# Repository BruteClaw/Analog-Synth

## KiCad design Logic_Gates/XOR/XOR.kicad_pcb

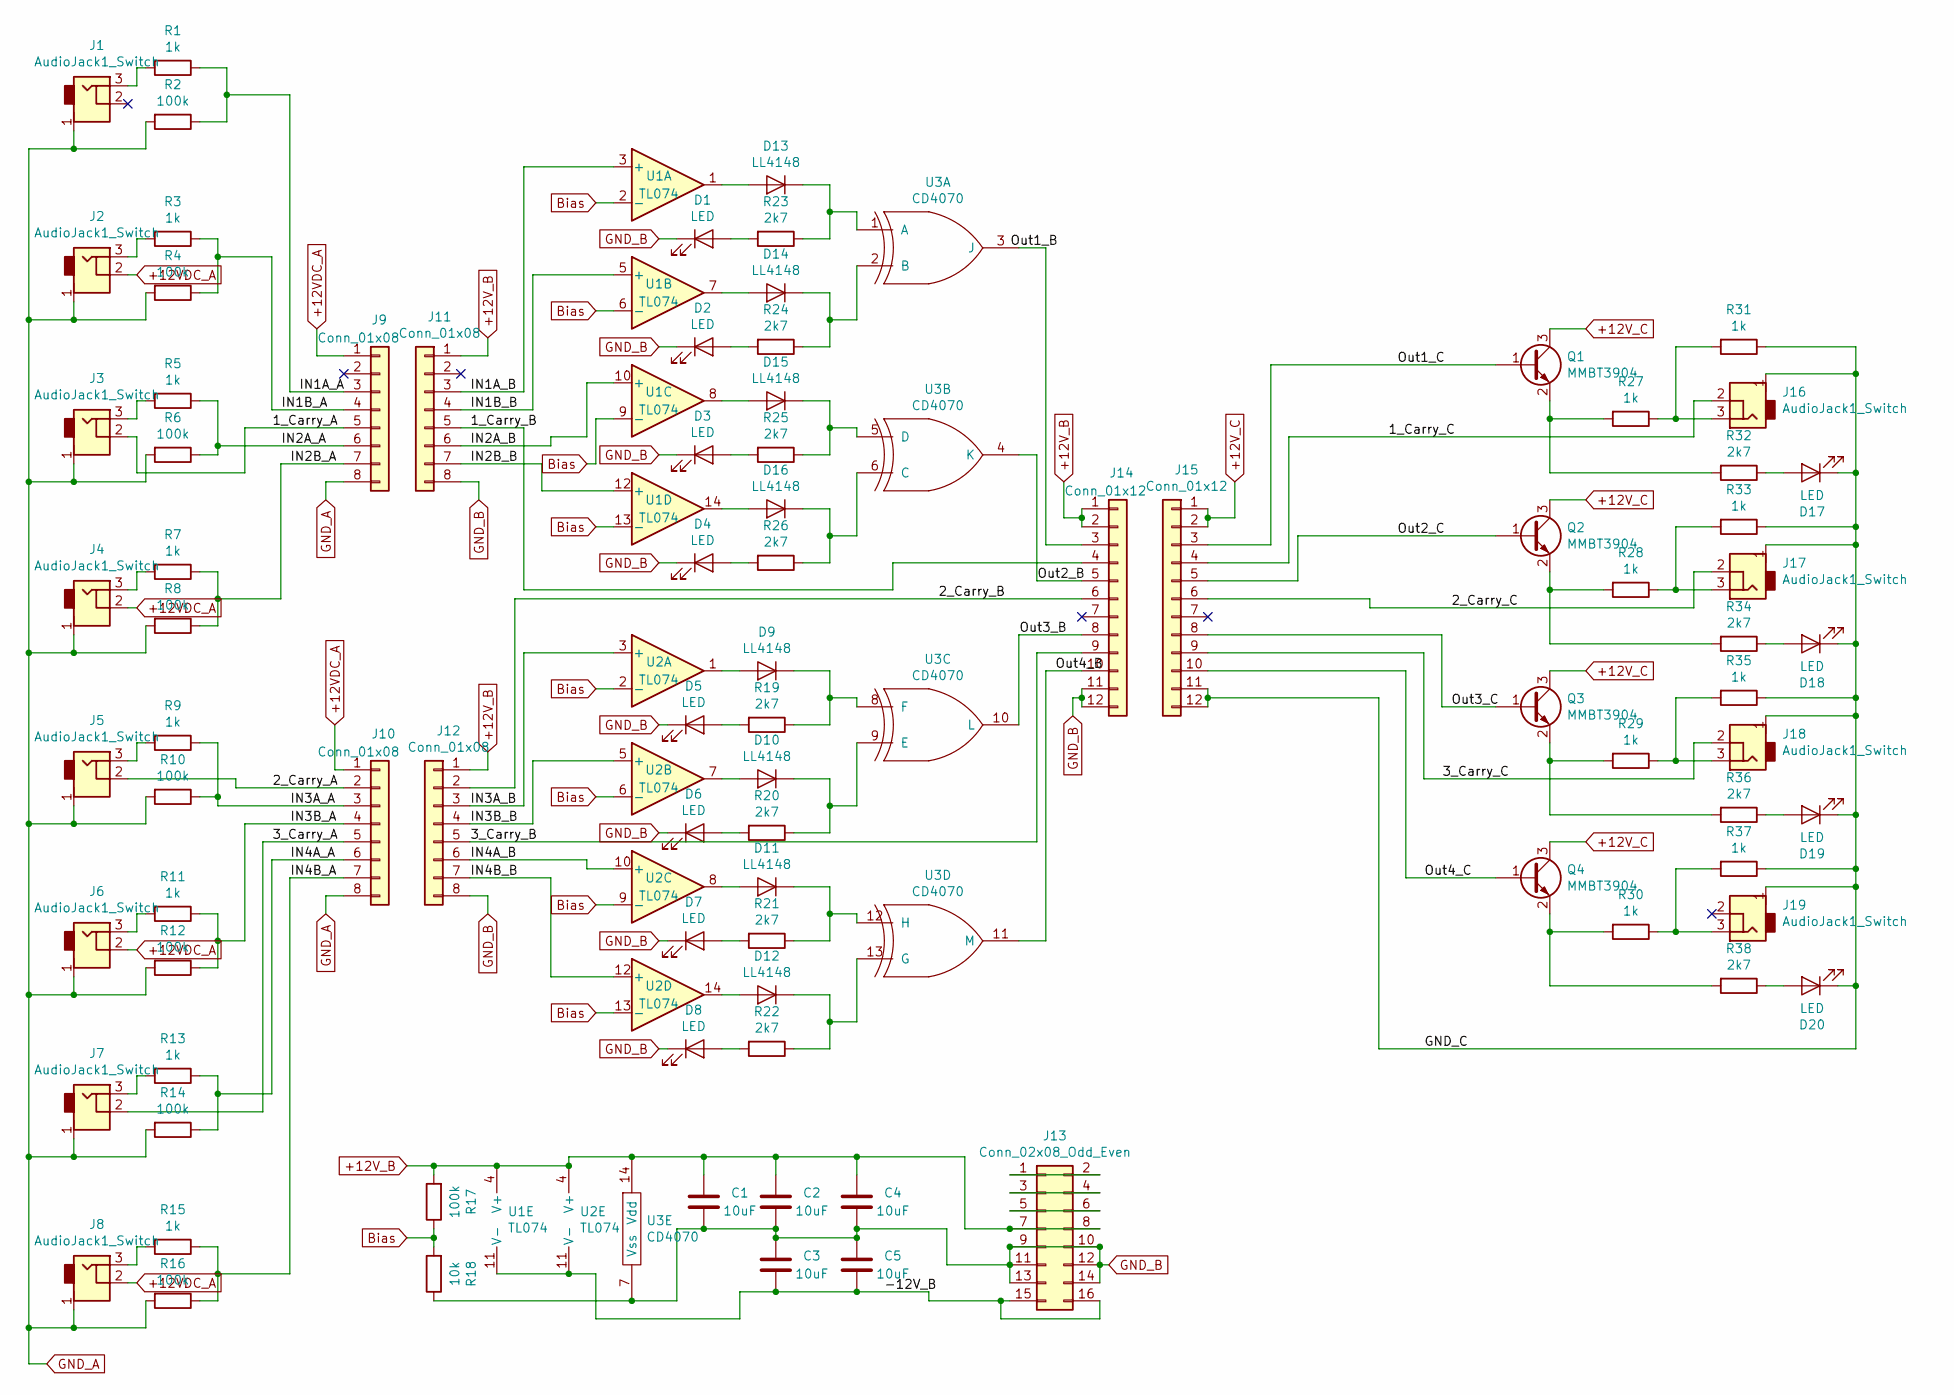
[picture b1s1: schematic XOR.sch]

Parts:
C1, C2, C3, C4, C5: 10uF; C_1210_HandSoldering
D1, D2, D3, D4, D5, D6, D7, D8, D17, D18, D19, D20: LED; LED_Rectangular_W3.9mm_H1.9mm
D9, D10, D11, D12, D13, D14, D15, D16: LL4148; D_MiniMELF_Handsoldering
J1, J2, J3, J4, J5, J6, J7, J8, J16, J17, J18, J19: AudioJack1_Switch; Mono_Jack_3.5mm_Switch_Switchcraft_35RAPC2AH3
J9, J10, J11, J12: Conn_01x08; Pin_Header_Straight_1x08_Pitch2.54mm
J13: Conn_02x08_Odd_Even; Pin_Header_Straight_2x08_Pitch2.54mm
J14, J15: Conn_01x12; Pin_Header_Straight_1x12_Pitch2.54mm
Q1, Q2, Q3, Q4: MMBT3904; SOT-23
R1, R3, R5, R7, R9, R11, R13, R15, R27, R28, R29, R30, R31, R33, R35, R37: 1k; R_1210_HandSoldering
R2, R4, R6, R8, R10, R12, R14, R16, R17: 100k; R_1210_HandSoldering
R18: 10k; R_1210_HandSoldering
R19, R20, R21, R22, R23, R24, R25, R26, R32, R34, R36, R38: 2k7; R_1210_HandSoldering
U1, U2: TL074; SOIC-14_3.9x8.7mm_Pitch1.27mm
U3: CD4070; SOIC-14_3.9x8.7mm_Pitch1.27mm

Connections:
+12VDC_A: J2.2, J4.2, J6.2, J8.2, J9.1, J10.1
+12V_B: C1.2, C2.2, C4.2, J11.1, J12.1, J13.7, J13.8, J14.1, J14.2, R17.2, U1.4 (V+), U2.4 (V+), U3.14 (Vdd)
+12V_C: J15.1, J15.2, Q1.3 (C), Q2.3 (C), Q3.3 (C), Q4.3 (C)
/1_Carry_A: J3.2, J9.5
/1_Carry_B: J11.5, J14.4
/1_Carry_C: J15.4, J16.2
/2_Carry_A: J5.2, J10.2
/2_Carry_B: J12.2, J14.6
/2_Carry_C: J15.6, J17.2
/3_Carry_A: J7.2, J10.5
/3_Carry_B: J12.5, J14.9
/3_Carry_C: J15.9, J18.2
/-12V_B: C3.1, C5.1, J13.15, J13.16, U1.11 (V-), U2.11 (V-)
/GND_C: D17.1 (K), D18.1 (K), D19.1 (K), D20.1 (K), J15.11, J15.12, J16.1, J17.1, J18.1, J19.1, R31.1, R33.1, R35.1, R37.1
/IN1A_A: J9.3, R1.1, R2.1
/IN1A_B: J11.3, U1.3 (+)
/IN1B_A: J9.4, R3.1, R4.1
/IN1B_B: J11.4, U1.5 (+)
/IN2A_A: J9.6, R5.1, R6.1
/IN2A_B: J11.6, U1.10 (+)
/IN2B_A: J9.7, R7.1, R8.1
/IN2B_B: J11.7, U1.12 (+)
/IN3A_A: J10.3, R9.1, R10.1
/IN3A_B: J12.3, U2.3 (+)
/IN3B_A: J10.4, R11.1, R12.1
/IN3B_B: J12.4, U2.5 (+)
/IN4A_A: J10.6, R13.1, R14.1
/IN4A_B: J12.6, U2.10 (+)
/IN4B_A: J10.7, R15.1, R16.1
/IN4B_B: J12.7, U2.12 (+)
/Out1_C: J15.3, Q1.1 (B)
/Out2_B: J14.5, U3.4 (K)
/Out2_C: J15.5, Q2.1 (B)
/Out3_B: J14.8, U3.10 (L)
/Out3_C: J15.8, Q3.1 (B)
/Out4_B: J14.10, U3.11 (M)
/Out4_C: J15.10, Q4.1 (B)
Bias: R17.1, R18.2, U1.2 (-), U1.6 (-), U1.9 (-), U1.13 (-), U2.2 (-), U2.6 (-), U2.9 (-), U2.13 (-)
GND_A: J1.1, J2.1, J3.1, J4.1, J5.1, J6.1, J7.1, J8.1, J9.8, J10.8, R2.2, R4.2, R6.2, R8.2, R10.2, R12.2, R14.2, R16.2
GND_B: C1.1, C2.1, C3.2, C4.1, C5.2, D1.1 (K), D2.1 (K), D3.1 (K), D4.1 (K), D5.1 (K), D6.1 (K), D7.1 (K), D8.1 (K), J11.8, J12.8, J13.9, J13.10, J13.11, J13.12, J13.13, J13.14, J14.11, J14.12, R18.1, U3.7 (Vss)
unnamed: D1.2 (A), R23.2
unnamed: D2.2 (A), R24.2
unnamed: D3.2 (A), R25.2
unnamed: D4.2 (A), R26.2
unnamed: D5.2 (A), R19.2
unnamed: D6.2 (A), R20.2
unnamed: D7.2 (A), R21.2
unnamed: D8.2 (A), R22.2
unnamed: D9.1 (K), R19.1, U3.8 (F)
unnamed: D9.2 (A), U2.1
unnamed: D10.1 (K), R20.1, U3.9 (E)
unnamed: D10.2 (A), U2.7
unnamed: D11.1 (K), R21.1, U3.12 (H)
unnamed: D11.2 (A), U2.8
unnamed: D12.1 (K), R22.1, U3.13 (G)
unnamed: D12.2 (A), U2.14
unnamed: D13.1 (K), R23.1, U3.1 (A)
unnamed: D13.2 (A), U1.1
unnamed: D14.1 (K), R24.1, U3.2 (B)
unnamed: D14.2 (A), U1.7
unnamed: D15.1 (K), R25.1, U3.5 (D)
unnamed: D15.2 (A), U1.8
unnamed: D16.1 (K), R26.1, U3.6 (C)
unnamed: D16.2 (A), U1.14
unnamed: D17.2 (A), R32.1
unnamed: D18.2 (A), R34.1
unnamed: D19.2 (A), R36.1
unnamed: D20.2 (A), R38.1
unnamed: J1.3, R1.2
unnamed: J2.3, R3.2
unnamed: J3.3, R5.2
unnamed: J4.3, R7.2
unnamed: J5.3, R9.2
unnamed: J6.3, R11.2
unnamed: J7.3, R13.2
unnamed: J8.3, R15.2
unnamed: J13.1, J13.2
unnamed: J13.3, J13.4
unnamed: J13.5, J13.6
unnamed: J14.3, U3.3 (J)
unnamed: J16.3, R27.1, R31.2
unnamed: J17.3, R28.1, R33.2
unnamed: J18.3, R29.1, R35.2
unnamed: J19.3, R30.1, R37.2
unnamed: Q1.2 (E), R27.2, R32.2
unnamed: Q2.2 (E), R28.2, R34.2
unnamed: Q3.2 (E), R29.2, R36.2
unnamed: Q4.2 (E), R30.2, R38.2

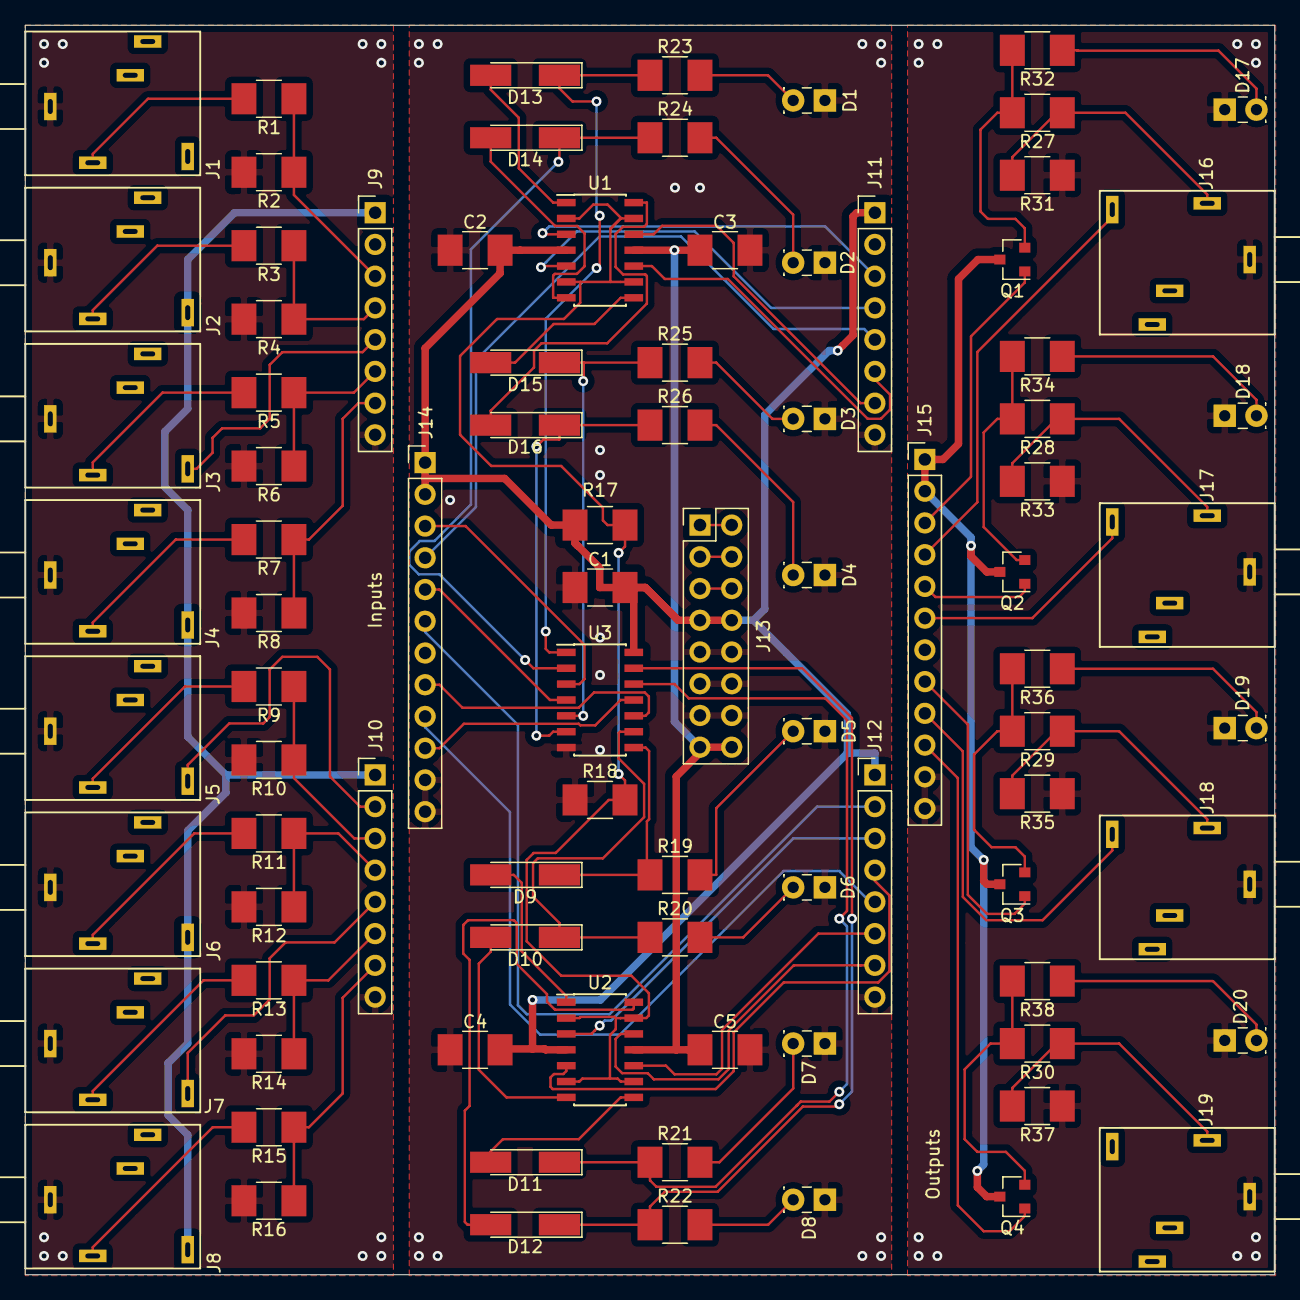
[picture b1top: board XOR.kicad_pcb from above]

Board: 2 copper layers, 100.0 x 100.0 mm, 89 parts (0 on the bottom side), 88 nets.

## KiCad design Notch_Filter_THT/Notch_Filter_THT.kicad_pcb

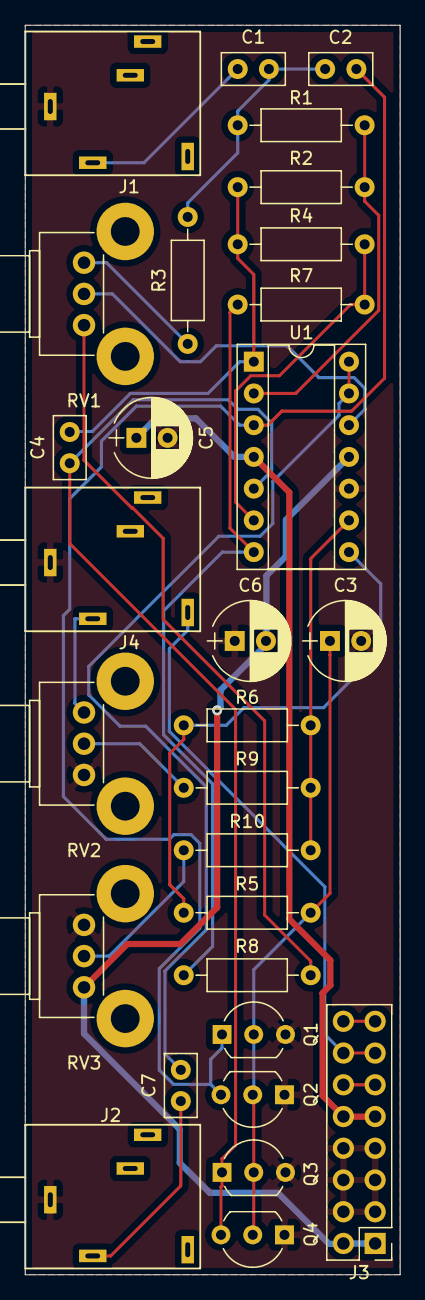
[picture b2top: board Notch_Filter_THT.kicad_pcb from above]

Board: 2 copper layers, 30.0 x 100.0 mm, 29 parts (0 on the bottom side), 25 nets.

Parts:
C1, C7: 10uF; C_Disc_D5.0mm_W2.5mm_P2.50mm
C2, C4: 15uF; C_Disc_D5.0mm_W2.5mm_P2.50mm
C3, C5, C6: 100uF; CP_Radial_D6.3mm_P2.50mm
J1, J2, J4: AudioJack1_Switch; Mono_Jack_3.5mm_Switch_Switchcraft_35RAPC2AH3
J3: Conn_02x08_Odd_Even; Pin_Header_Straight_2x08_Pitch2.54mm
Q1, Q2, Q3, Q4: 2N3904; TO-92_Inline_Wide
R1, R2, R4, R7: 22K; R_Axial_DIN0207_L6.3mm_D2.5mm_P10.16mm_Horizontal
R3, R8: 10K; R_Axial_DIN0207_L6.3mm_D2.5mm_P10.16mm_Horizontal
R5: 4K7; R_Axial_DIN0207_L6.3mm_D2.5mm_P10.16mm_Horizontal
R6, R9, R10: 100K; R_Axial_DIN0207_L6.3mm_D2.5mm_P10.16mm_Horizontal
RV1, RV2, RV3: 500K; Potentiometer_Bourns_PTV09A-2_Vertical
U1: TL074; DIP-14_W7.62mm_Socket

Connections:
GND: C3.2, C5.2, C6.1, J1.1, J2.1, J3.3, J3.4, J3.5, J3.6, J3.7, J3.8, J4.1, Q1.3, Q2.1, Q3.3, Q4.1, RV2.3, RV3.1, U1.10
unnamed: C1.1, C2.2, R1.2, R3.2
unnamed: C1.2, J1.3
unnamed: C2.1, Q1.1, Q2.3, U1.3
unnamed: C3.1, Q1.2, Q2.2, Q3.2, Q4.2, R5.1
unnamed: C4.1, Q3.1, Q4.3, U1.5
unnamed: C4.2, R2.1, R4.2, U1.1
unnamed: C5.1, J3.9, J3.10, U1.4
unnamed: C6.2, J3.1, J3.2, RV3.3, U1.11
unnamed: C7.1, J2.3
unnamed: C7.2, U1.13, U1.14
unnamed: J3.11, J3.12
unnamed: J3.13, J3.14, J4.2
unnamed: J3.15, J3.16
unnamed: J4.3, RV2.1
unnamed: R1.1, R2.2, U1.2
unnamed: R3.1, RV1.1
unnamed: R4.1, R7.2, U1.6
unnamed: R5.2, R6.2, U1.8
unnamed: R7.1, R8.1, U1.7
unnamed: R8.2, RV1.3
unnamed: R9.1, RV2.2
unnamed: R10.1, RV3.2
unnamed: R6.1, R9.2, R10.2, U1.9
unnamed: RV1.2, U1.12

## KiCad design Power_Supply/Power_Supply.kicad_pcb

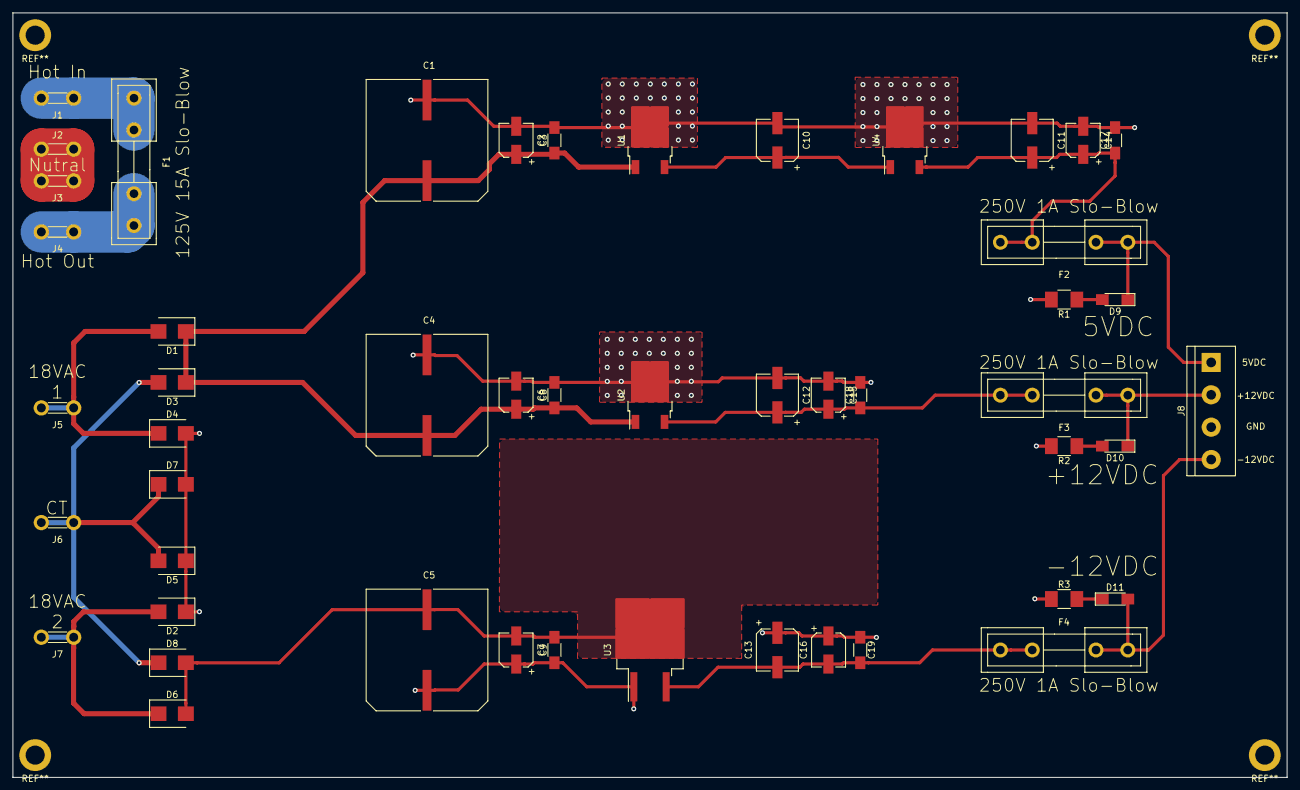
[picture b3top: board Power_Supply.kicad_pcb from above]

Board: 2 copper layers, 200.0 x 120.0 mm, 49 parts (0 on the bottom side), 19 nets.

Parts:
C1, C4, C5: 2200uF; CP_Elec_18 x 21.5
C2, C6, C7, C14, C15, C16: 10uF; CP_Elec_5x5.3
C3, C8, C9, C17, C18, C19: 0.1uF; C_1206_HandSoldering
C10, C11, C12, C13: 22uF; CP_Elec_6.3x5.7
D1, D2, D3, D4, D5, D6, D7, D8: D; D_SMB
D9, D10, D11: LED; LED_1206_HandSoldering
F1, F2, F3, F4: Fuse; Fuseholder5x20_horiz_open_inline_Type-I
J1: Hot_In; TAB_Conn
J2: Netral_IN; TAB_Conn
J3: Nutral_Out; TAB_Conn
J4: Hot_Out; TAB_Conn
J5: 18VAC_1; TAB_Conn
J6: CT; TAB_Conn
J7: 18VAC_2; TAB_Conn
J8: Screw_Terminal_01x04; TerminalBlock_bornier-4_P5.08mm
R1: 150; R_1210_HandSoldering
R2, R3: 560; R_1210_HandSoldering
U1, U2: L7812; TO-252-2
U3: L7912; TO-263-2
U4: L7805; TO-252-2

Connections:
/0VDC: C1.2, C2.2, C3.2, C4.2, C5.1, C6.2, C7.1, C8.2, C9.1, C10.2, C11.2, C12.2, C13.1, C14.2, C15.2, C16.1, C17.2, C18.2, C19.1, D2.1, D4.2, D5.1, D7.2, J8.3, R1.2, R2.2, R3.1, U1.2, U2.2, U3.1, U4.2
/18VAC_1: D1.2, D4.1, J5.1
/18VAC_2: D2.2, D6.1, J7.1
/+5VDC: C11.1, C14.1, C17.1, F2.2, U4.3
/+12VDC: C12.1, C15.1, C18.1, F3.2, U2.3
/+18VDC: C1.1, C2.1, C3.1, C4.1, C6.1, C8.1, D1.1, D3.1, U1.1, U2.1
/-12VDC: C13.2, C16.2, C19.2, F4.2, U3.3
/-18VDC: C5.2, C7.2, C9.2, D6.2, D8.2, U3.2
/HOT_IN: F1.1, J1.1
/HOT_OUT: F1.2, J4.1
/NUT: J2.1, J3.1
GNDPWR: D3.2, D5.2, D7.1, D8.1, J6.1
unnamed: C10.1, U1.3, U4.1
unnamed: D9.1, F2.1, J8.1
unnamed: D9.2, R1.1
unnamed: D10.1, F3.1, J8.2
unnamed: D10.2, R2.1
unnamed: D11.1, R3.2
unnamed: D11.2, F4.1, J8.4

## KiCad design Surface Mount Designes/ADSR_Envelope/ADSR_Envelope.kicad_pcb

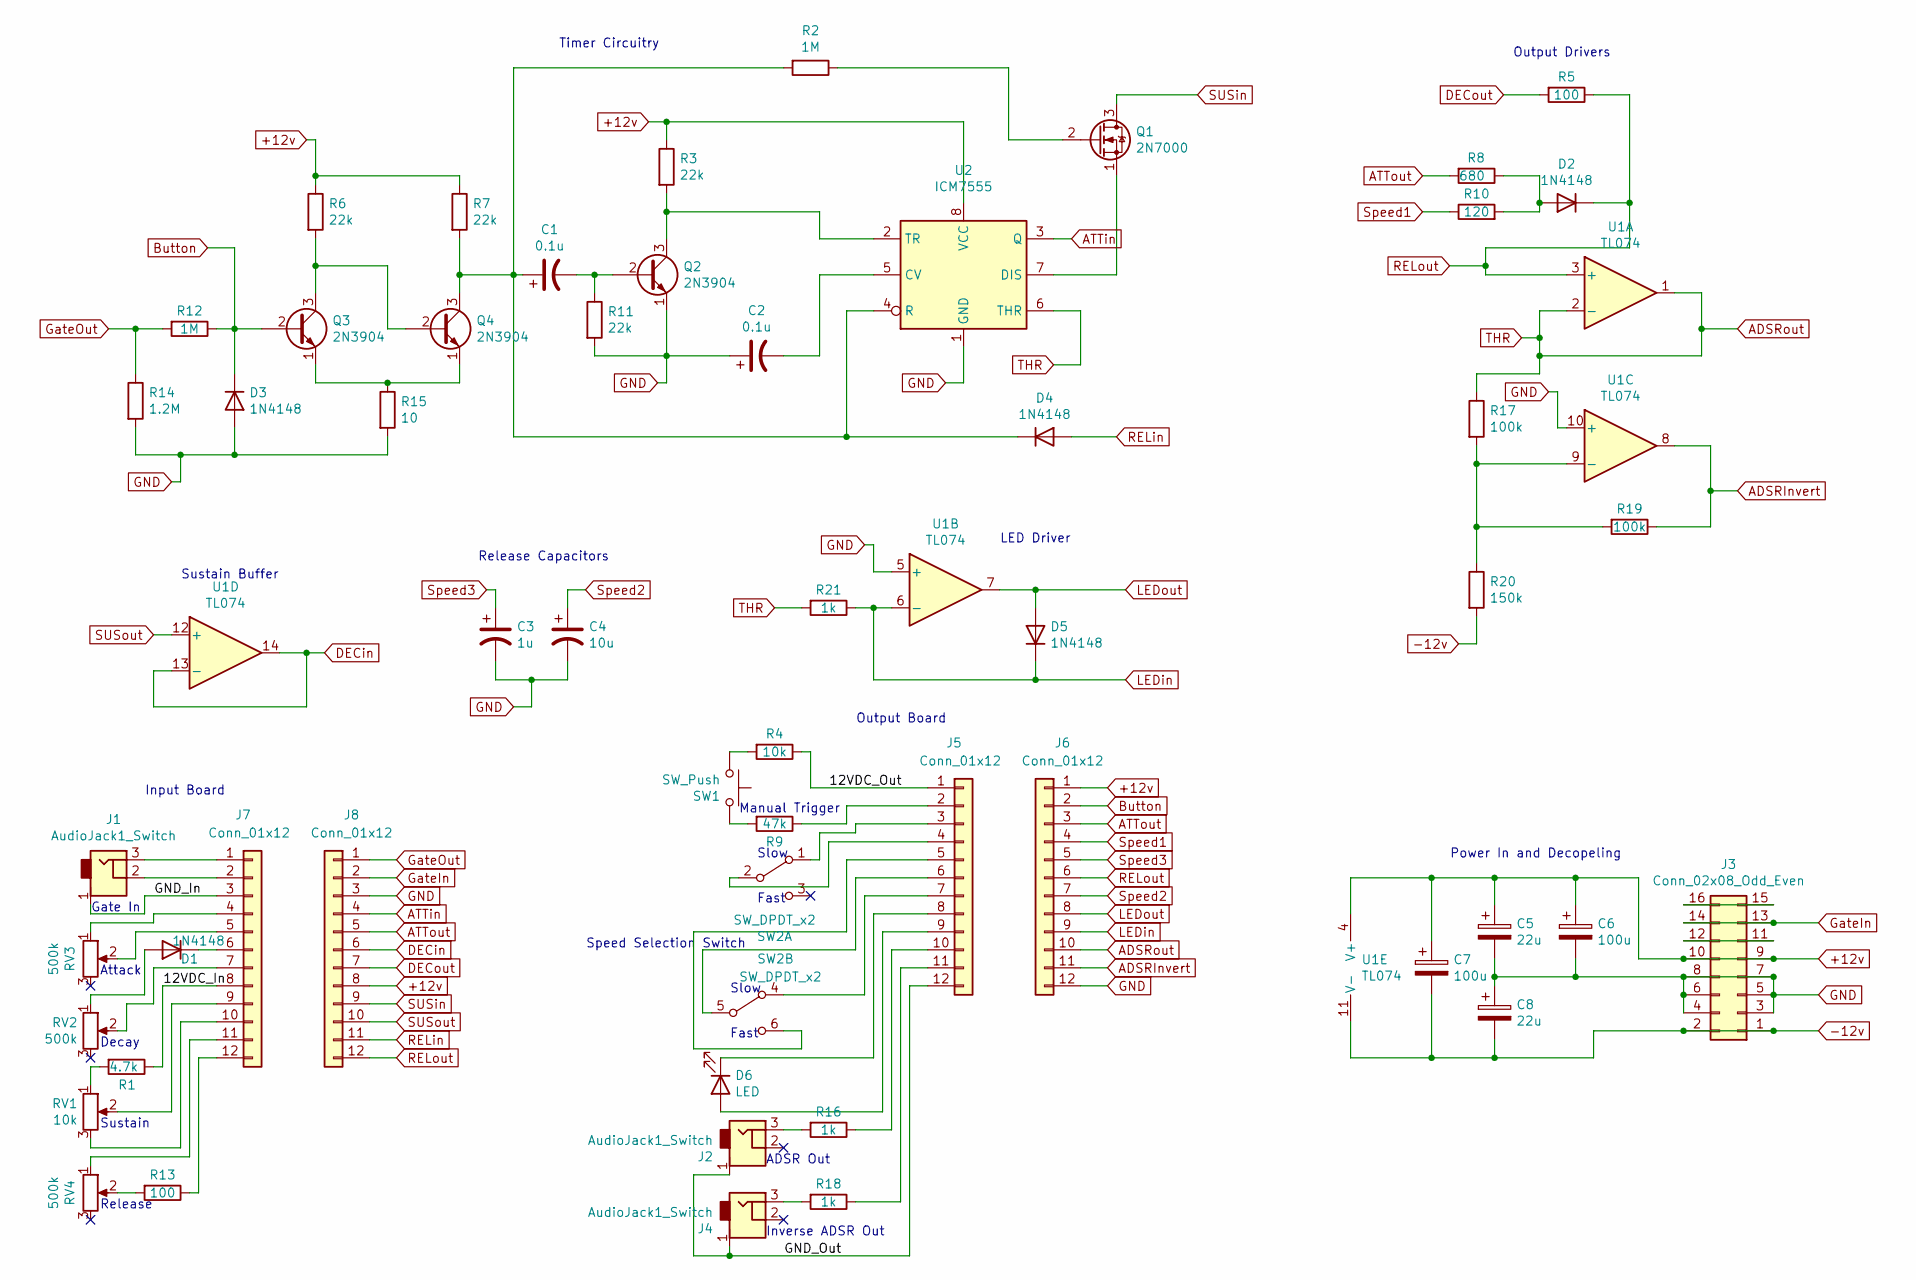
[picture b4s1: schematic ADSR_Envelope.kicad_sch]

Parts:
C1, C2: 0.1u; C_1210_HandSoldering
C3: 1u; C_1210_HandSoldering
C4: 10u; C_1210_HandSoldering
C5, C8: 22u; C_1210_HandSoldering
C6, C7: 100u; C_1210_HandSoldering
D1, D2, D3, D4, D5: 1N4148; D_SOD-123
D6: LED; LED_Rectangular_W3.9mm_H1.9mm
J1, J2, J4: AudioJack1_Switch; Mono_Jack_3.5mm_Switch_Switchcraft_35RAPC2AH3
J3: Conn_02x08_Odd_Even; Pin_Header_Straight_2x08_Pitch2.54mm
J5, J6, J7, J8: Conn_01x12; Pin_Header_Straight_1x12_Pitch2.54mm
Q1: 2N7000; SOT-23
Q2, Q3, Q4: 2N3904; SOT-23
R1: 4.7k; R_1210_HandSoldering
R2, R12: 1M; R_1210_HandSoldering
R3, R6, R7, R11: 22k; R_1210_HandSoldering
R4: 10k; R_1210_HandSoldering
R5, R13: 100; R_1210_HandSoldering
R8: 680; R_1210_HandSoldering
R9: 47k; R_1210_HandSoldering
R10: 120; R_1210_HandSoldering
R14: 1.2M; R_1210_HandSoldering
R15: 10; R_1210_HandSoldering
R16, R18, R21: 1k; R_1210_HandSoldering
R17, R19: 100k; R_1210_HandSoldering
R20: 150k; R_1210_HandSoldering
RV1: 10k; Potentiometer_Bourns_PTV09A-2_Vertical
RV2, RV3, RV4: 500k; Potentiometer_Bourns_PTV09A-2_Vertical
SW1: SW_Push; SW_Tactile_TE_FSMRACDAH
SW2: SW_DPDT_x2; 200AWMDP1T2A1M6QE
U1: TL074; SOIC-14_N
U2: ICM7555; SOIC-8-N

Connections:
+12v: C5.1, C6.1, C7.1, J3.9, J3.10, J6.1, J8.8, R3.1, R6.1, R7.1, U1.4 (V+), U2.8 (VCC)
-12v: C7.2, C8.2, J3.1, J3.2, R20.2, U1.11 (V-)
/12VDC_In: J7.8, R1.1
/12VDC_Out: J5.1, R4.1
/GND_In: J1.1, J7.3
/GND_Out: J2.1, J4.1, J5.12
ADSRInvert: J6.11, R19.1, U1.8
ADSRout: J6.10, R17.1, R21.2, U1.1, U1.2 (-), U2.6 (THR)
ATTin: J8.4, U2.3 (Q)
ATTout: J6.3, J8.5, R8.2
Button: D3.1 (K), J6.2, Q3.2 (B), R12.1
DECin: J8.6, U1.13 (-), U1.14
DECout: J8.7, R5.2
GND: C2.1, C3.2, C4.2, C5.2, C6.2, C8.1, D3.2 (A), J3.3, J3.4, J3.5, J3.6, J3.7, J3.8, J6.12, J8.3, Q2.1 (E), R11.2, R14.2, R15.2, U1.5 (+), U1.10 (+), U2.1 (GND)
GateIn: J3.13, J3.14, J8.2
GateOut: J8.1, R12.2, R14.1
LEDin: D5.1 (K), J6.9, R21.1, U1.6 (-)
LEDout: D5.2 (A), J6.8, U1.7
unnamed: C1.1, D4.1 (K), Q4.3 (C), R2.2, R7.2, U2.4 (R)
unnamed: C1.2, Q2.2 (B), R11.1
unnamed: C2.2, U2.5 (CV)
unnamed: D1.1 (K), J7.6
unnamed: D1.2 (A), RV2.1
unnamed: D2.2 (A), R8.1, R10.2
unnamed: D6.1 (K), J5.8
unnamed: D6.2 (A), J5.9
unnamed: J1.2, J7.2
unnamed: J1.3, J7.1
unnamed: J2.3, R16.2
unnamed: J3.11, J3.12
unnamed: J3.15, J3.16
unnamed: J4.3, R18.2
unnamed: J5.2, R9.1
unnamed: J5.3, SW2.1 (A)
unnamed: J5.4, SW2.2 (B)
unnamed: J5.5, SW2.6 (C)
unnamed: J5.6, SW2.5 (B)
unnamed: J5.7, SW2.4 (A)
unnamed: J5.10, R16.1
unnamed: J5.11, R18.1
unnamed: J7.4, RV3.1
unnamed: J7.5, RV3.2
unnamed: J7.7, RV2.2
unnamed: J7.9, RV1.2
unnamed: J7.10, RV1.3
unnamed: J7.11, RV4.1
unnamed: J7.12, R13.1
unnamed: Q1.1 (S), U2.7 (DIS)
unnamed: Q1.2 (G), R2.1
unnamed: Q2.3 (C), R3.2, U2.2 (TR)
unnamed: Q3.1 (E), Q4.1 (E), R15.1
unnamed: Q3.3 (C), Q4.2 (B), R6.2
unnamed: R1.2, RV1.1
unnamed: R4.2, SW1.1
unnamed: R9.2, SW1.2
unnamed: R13.2, RV4.2
unnamed: R17.2, R19.2, R20.1, U1.9 (-)
RELin: D4.2 (A), J8.11
RELout: D2.1 (K), J6.6, J8.12, R5.1, U1.3 (+)
SUSin: J8.9, Q1.3 (D)
SUSout: J8.10, U1.12 (+)
Speed1: J6.4, R10.1
Speed2: C4.1, J6.7
Speed3: C3.1, J6.5

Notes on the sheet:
ADSR Out
Slow
Manual Trigger
Gate In
Sustain Buffer
Attack
Speed Selection Switch
Decay
Timer Circuitry
LED Driver
Fast
Output Drivers
Inverse ADSR Out
Output Board
Input Board
Release Capacitors
Sustain
Release
Power In and Decopeling

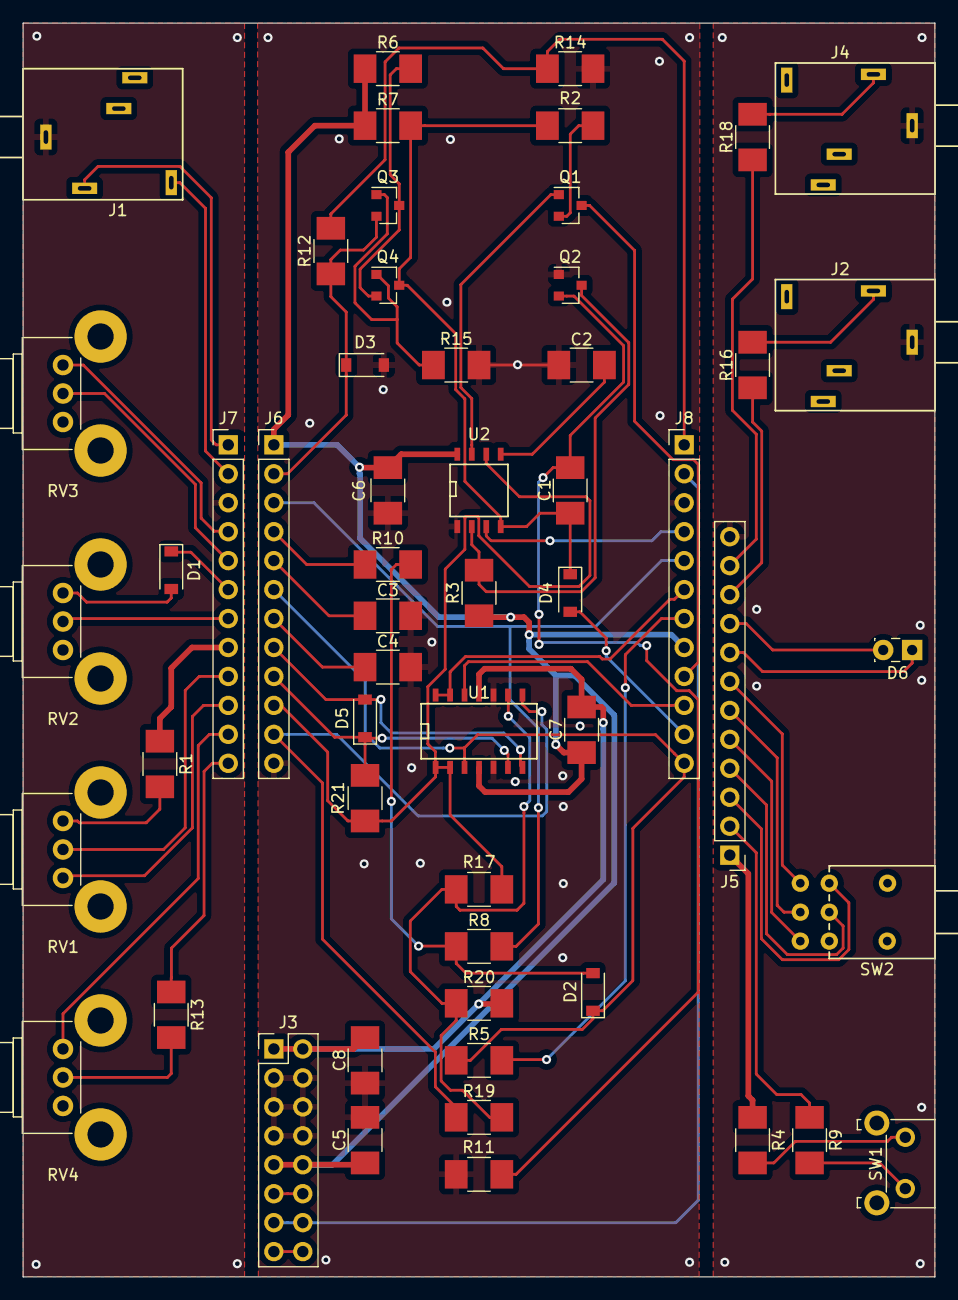
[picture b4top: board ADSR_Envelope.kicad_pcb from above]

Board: 2 copper layers, 80.0 x 110.0 mm, 55 parts (0 on the bottom side), 64 nets.

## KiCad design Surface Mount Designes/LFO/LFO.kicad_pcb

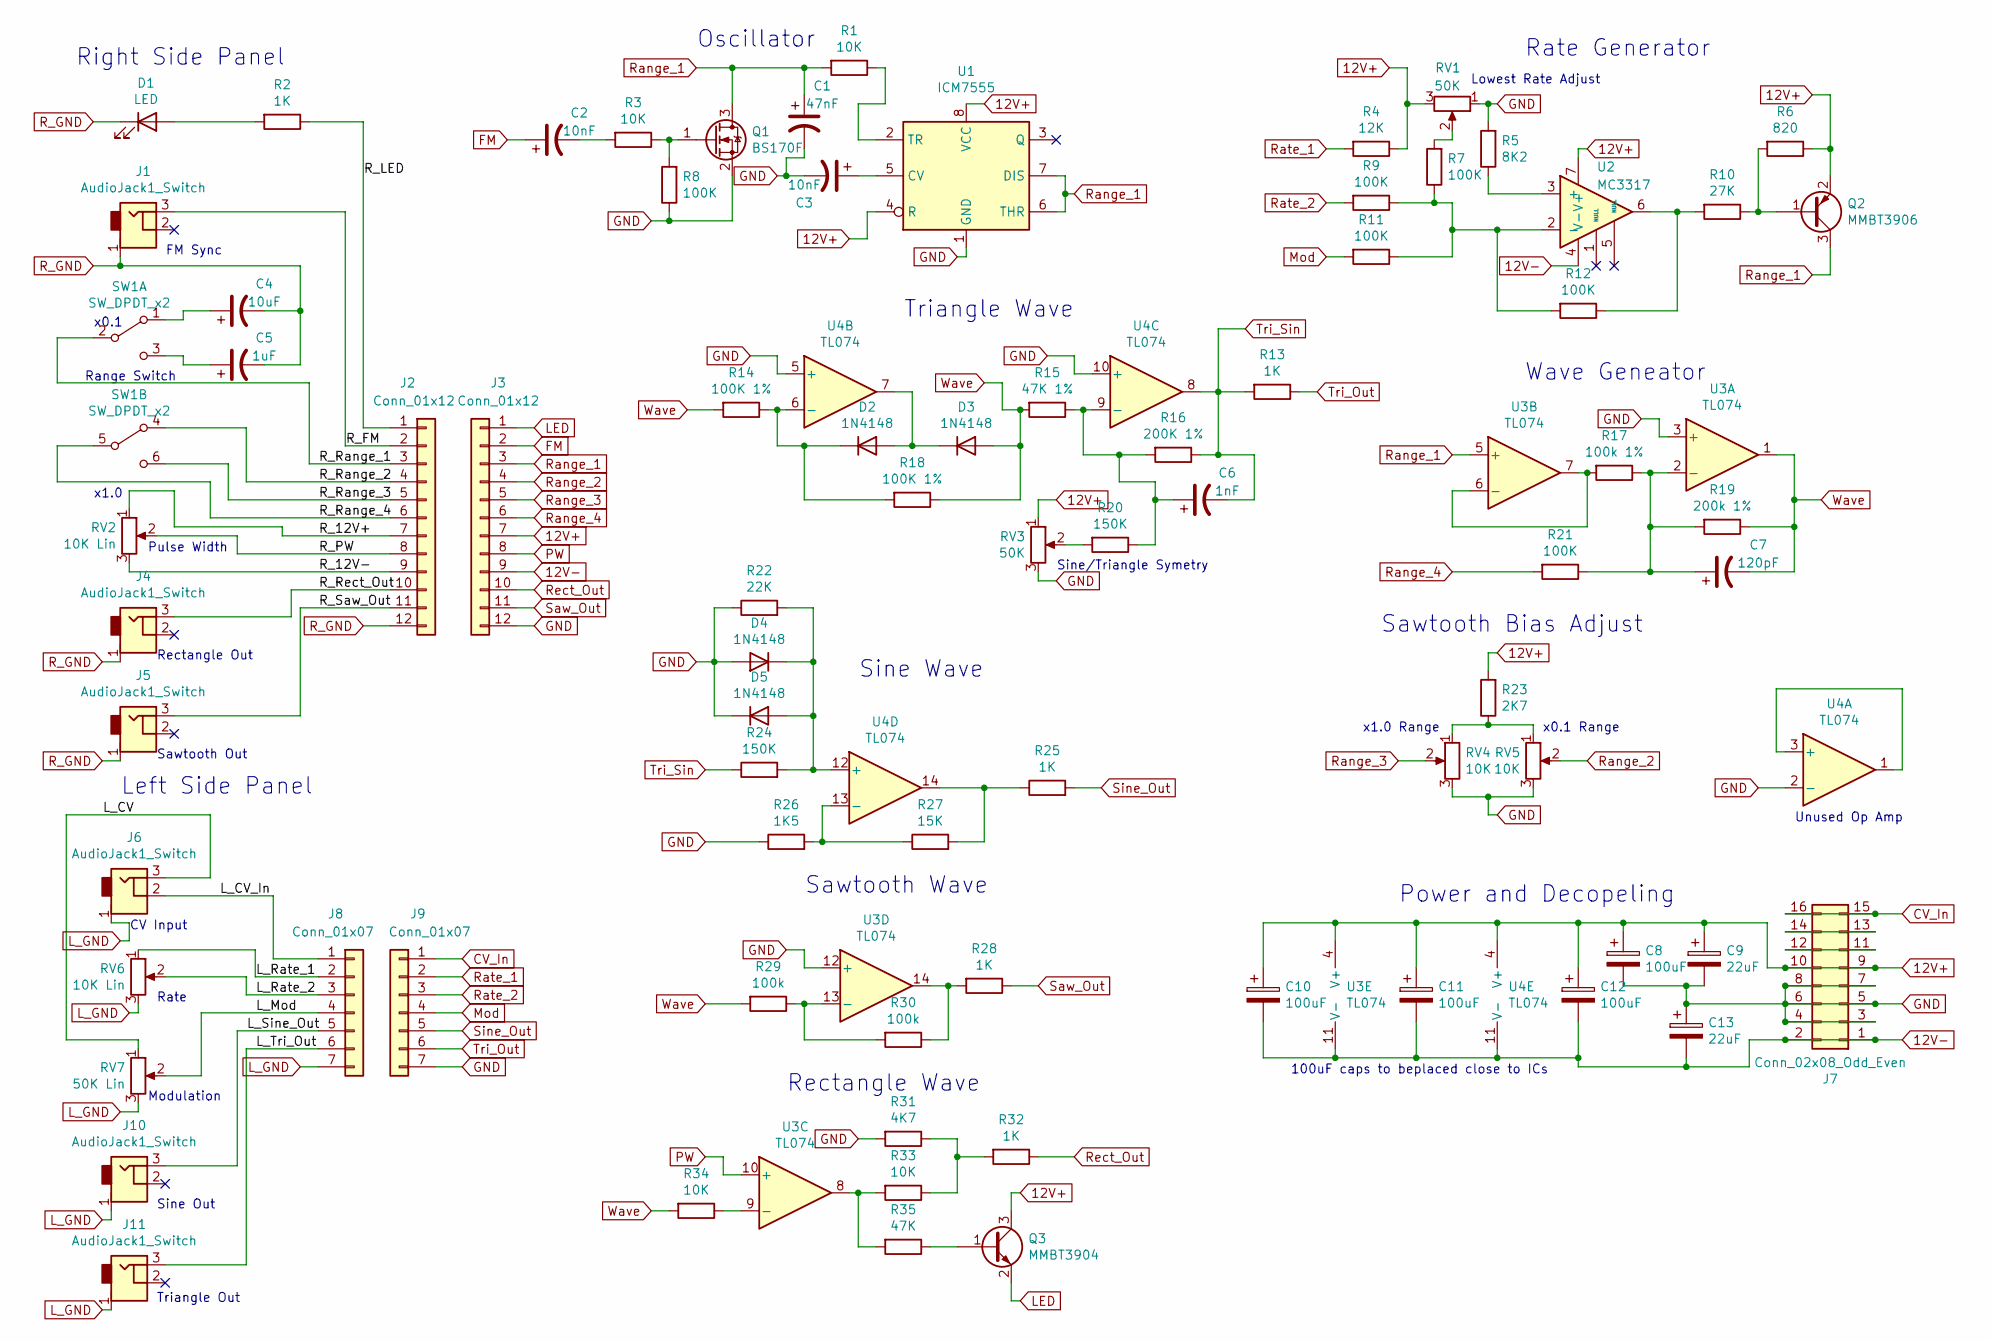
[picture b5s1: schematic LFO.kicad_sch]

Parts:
C1: 47nF; C_1210_HandSoldering
C2, C3: 10nF; C_1210_HandSoldering
C4: 10uF; C_1210_HandSoldering
C5: 1uF; C_1210_HandSoldering
C6: 1nF; C_1210_HandSoldering
C7: 120pF; C_1210_HandSoldering
C8, C10, C11, C12: 100uF; CP_Elec_6.3x5.8
C9, C13: 22uF; CP_Elec_5x5.8
D1: LED; LED_Rectangular_W3.9mm_H1.9mm
D2, D3, D4, D5: 1N4148; D_SOD-123
J1, J4, J5, J6, J10, J11: AudioJack1_Switch; Mono_Jack_3.5mm_Switch_Switchcraft_35RAPC2AH3
J2, J3: Conn_01x12; Pin_Header_Straight_1x12_Pitch2.54mm
J7: Conn_02x08_Odd_Even; Pin_Header_Straight_2x08_Pitch2.54mm
J8, J9: Conn_01x07; Pin_Header_Straight_1x07_Pitch2.54mm
Q1: BS170F; SOT-23
Q2: MMBT3906; SOT-23
Q3: MMBT3904; SOT-23
R1, R3, R33, R34: 10K; R_1210_HandSoldering
R2, R13, R25, R28, R32: 1K; R_1210_HandSoldering
R4: 12K; R_1210_HandSoldering
R5: 8K2; R_1210_HandSoldering
R6: 820; R_1210_HandSoldering
R7, R8, R9, R11, R12, R21: 100K; R_1210_HandSoldering
R10: 27K; R_1210_HandSoldering
R14, R18: 100K 1%; R_1210_HandSoldering
R15: 47K 1%; R_1210_HandSoldering
R16: 200K 1%; R_1210_HandSoldering
R17: 100k 1%; R_1210_HandSoldering
R19: 200k 1%; R_1210_HandSoldering
R20, R24: 150K; R_1210_HandSoldering
R22: 22K; R_1210_HandSoldering
R23: 2K7; R_1210_HandSoldering
R26: 1K5; R_1210_HandSoldering
R27: 15K; R_1210_HandSoldering
R29, R30: 100k; R_1210_HandSoldering
R31: 4K7; R_1210_HandSoldering
R35: 47K; R_1210_HandSoldering
RV1, RV3: 50K; PVG5A
RV2, RV6: 10K Lin; Potentiometer_Bourns_PTV09A-2_Vertical
RV4, RV5: 10K; PVG5A
RV7: 50K Lin; Potentiometer_Bourns_PTV09A-2_Vertical
SW1: SW_DPDT_x2; 200AWMDP1T2A1M6QE
U1: ICM7555; SOIC-8_3.9x4.9mm_Pitch1.27mm
U2: MC3317; SO-8_5.3x6.2mm_Pitch1.27mm
U3, U4: TL074; SOIC-14_3.9x8.7mm_Pitch1.27mm

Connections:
12V+: C8.1, C9.1, C10.1, C11.1, C12.1, J3.7, J7.9, J7.10, Q2.2 (E), Q3.3 (C), R4.1, R6.1, R23.2, RV1.3, RV3.1, U1.4 (R), U1.8 (VCC), U2.7 (V+), U3.4 (V+), U4.4 (V+)
12V-: C10.2, C11.2, C12.2, C13.2, J3.9, J7.1, J7.2, U2.4 (V-), U3.11 (V-), U4.11 (V-)
/L_CV: J6.3, RV7.1
/L_CV_In: J6.2, J8.1
/L_Mod: J8.4, RV7.2
/L_Rate_1: J8.2, RV6.1
/L_Rate_2: J8.3, RV6.2
/L_Sine_Out: J8.5, J10.3
/L_Tri_Out: J8.6, J11.3
/R_12V+: J2.7, RV2.1
/R_12V-: J2.9, RV2.3
/R_FM: J1.3, J2.2
/R_LED: J2.1, R2.1
/R_PW: J2.8, RV2.2
/R_Range_1: J2.3, SW1.2 (B)
/R_Range_2: J2.4, SW1.4 (A)
/R_Range_3: J2.5, SW1.6 (C)
/R_Range_4: J2.6, SW1.5 (B)
/R_Rect_Out: J2.10, J4.3
/R_Saw_Out: J2.11, J5.3
CV_In: J7.15, J7.16, J9.1
FM: C2.1, J3.2
GND: C1.2, C3.2, C8.2, C9.2, C13.1, D4.2 (A), D5.1 (K), J3.12, J7.3, J7.4, J7.5, J7.6, J7.7, J7.8, J9.7, Q1.2 (S), R5.2, R8.1, R22.1, R26.1, R31.2, RV1.1, RV3.3, RV4.3, RV5.3, U1.1 (GND), U3.3 (+), U3.12 (+), U4.2 (-), U4.5 (+), U4.10 (+)
LED: J3.1, Q3.2 (E)
L_GND: J6.1, J8.7, J10.1, J11.1, RV6.3, RV7.3
Mod: J9.4, R11.2
unnamed: C2.2, R3.2
unnamed: C3.1, U1.5 (CV)
unnamed: C4.1, SW1.1 (A)
unnamed: C5.1, SW1.3 (C)
unnamed: C6.1, R15.1, R16.2, R20.1, U4.9 (-)
unnamed: C7.1, R17.1, R19.2, R21.1, U3.2 (-)
unnamed: D1.2 (A), R2.2
unnamed: D2.1 (K), R14.1, R18.2, U4.6 (-)
unnamed: D2.2 (A), D3.1 (K), U4.7
unnamed: D4.1 (K), D5.2 (A), R22.2, R24.2, U4.12 (+)
unnamed: J7.11, J7.12
unnamed: J7.13, J7.14
unnamed: Q1.1 (G), R3.1, R8.2
unnamed: Q2.1 (B), R6.2, R10.1
unnamed: Q3.1 (B), R35.1
unnamed: R1.1, U1.2 (TR)
unnamed: R5.1, U2.3 (+)
unnamed: R7.2, RV1.2
unnamed: R10.2, R12.1, U2.6
unnamed: R7.1, R9.1, R11.1, R12.2, U2.2 (-)
unnamed: R17.2, U3.6 (-), U3.7
unnamed: R20.2, RV3.2
unnamed: R23.1, RV4.1, RV5.1
unnamed: R25.1, R27.2, U4.14
unnamed: R26.2, R27.1, U4.13 (-)
unnamed: R28.2, R30.1, U3.14
unnamed: R29.1, R30.2, U3.13 (-)
unnamed: R31.1, R32.2, R33.1
unnamed: R33.2, R35.2, U3.8
unnamed: R34.1, U3.9 (-)
unnamed: U4.1, U4.3 (+)
PW: J3.8, U3.10 (+)
R_GND: C4.2, C5.2, D1.1 (K), J1.1, J2.12, J4.1, J5.1
Range_1: C1.1, J3.3, Q1.3 (D), Q2.3 (C), R1.2, U1.6 (THR), U1.7 (DIS), U3.5 (+)
Range_2: J3.4, RV5.2
Range_3: J3.5, RV4.2
Range_4: J3.6, R21.2
Rate_1: J9.2, R4.2
Rate_2: J9.3, R9.2
Rect_Out: J3.10, R32.1
Saw_Out: J3.11, R28.1
Sine_Out: J9.5, R25.2
Tri_Out: J9.6, R13.1
Tri_Sin: C6.2, R13.2, R16.1, R24.1, U4.8
Wave: C7.2, D3.2 (A), R14.2, R15.2, R18.1, R19.1, R29.2, R34.2, U3.1

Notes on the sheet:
x0.1
Sawtooth Out
Sawtooth Wave
Wave Geneator
Modulation
Rectangle Out
Sine/Triangle Symetry
Range Switch
Rate Generator
Sawtooth Bias Adjust
Triangle Wave
Unused Op Amp
x1.0
CV Input
Rate
x0.1 Range
Power and Decopeling
Left Side Panel
Lowest Rate Adjust
FM Sync
Rectangle Wave
Sine Wave
Triangle Out
x1.0 Range
Oscillator
100uF caps to beplaced close to ICs
Pulse Width
Right Side Panel
Sine Out

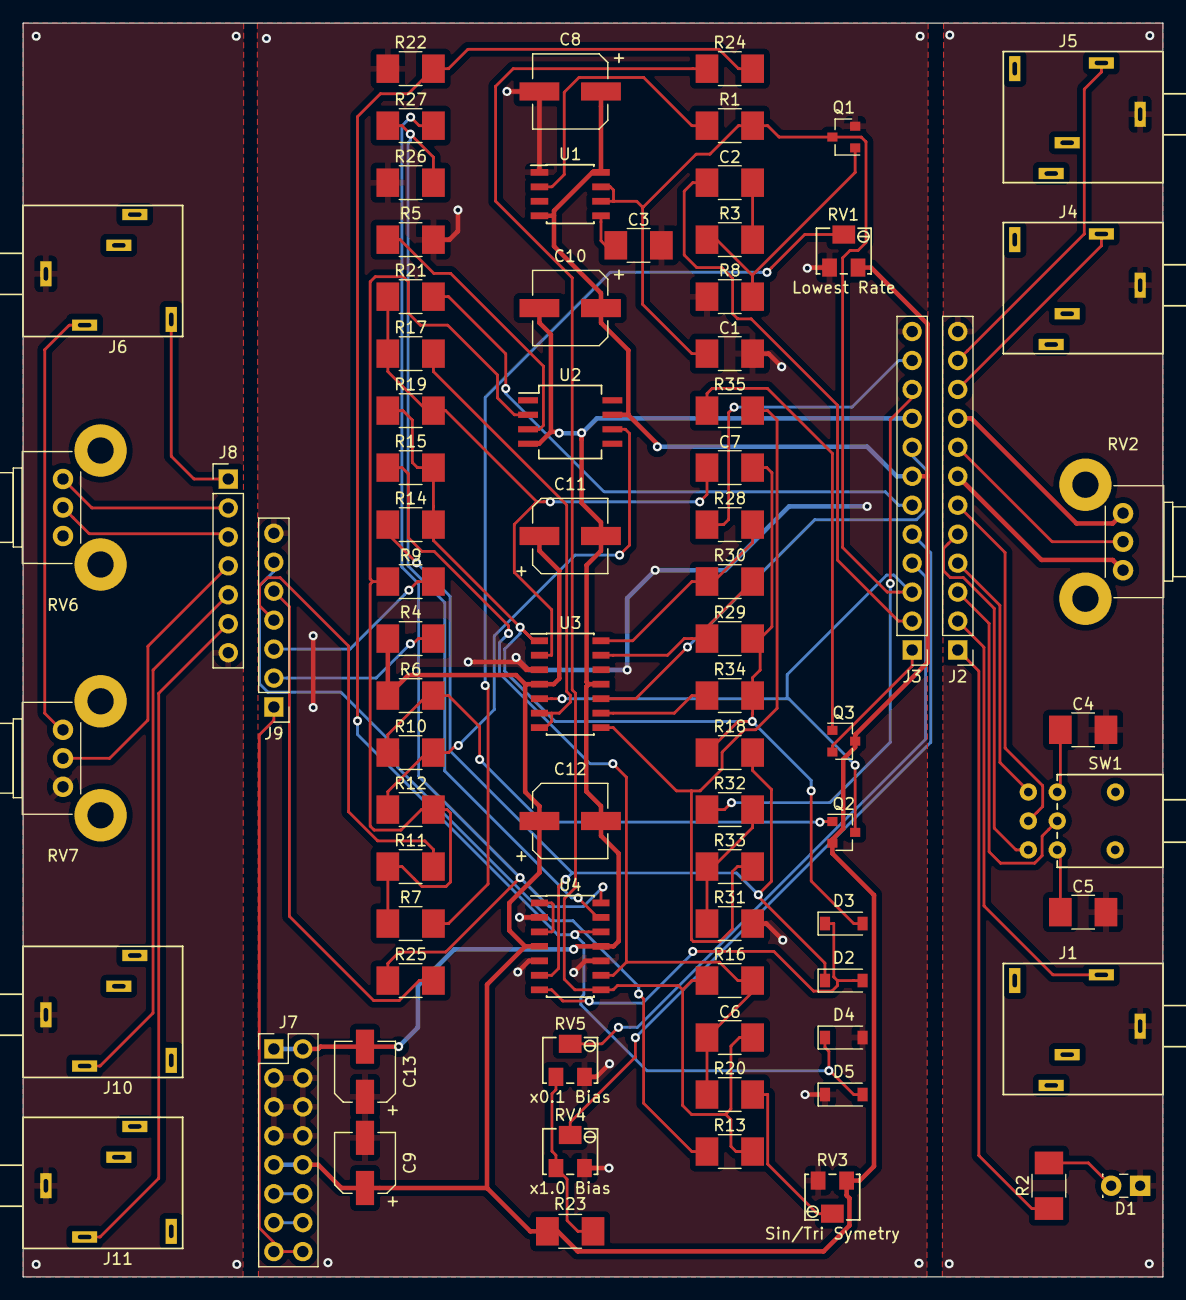
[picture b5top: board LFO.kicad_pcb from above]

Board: 2 copper layers, 100.0 x 110.0 mm, 79 parts (0 on the bottom side), 71 nets.
